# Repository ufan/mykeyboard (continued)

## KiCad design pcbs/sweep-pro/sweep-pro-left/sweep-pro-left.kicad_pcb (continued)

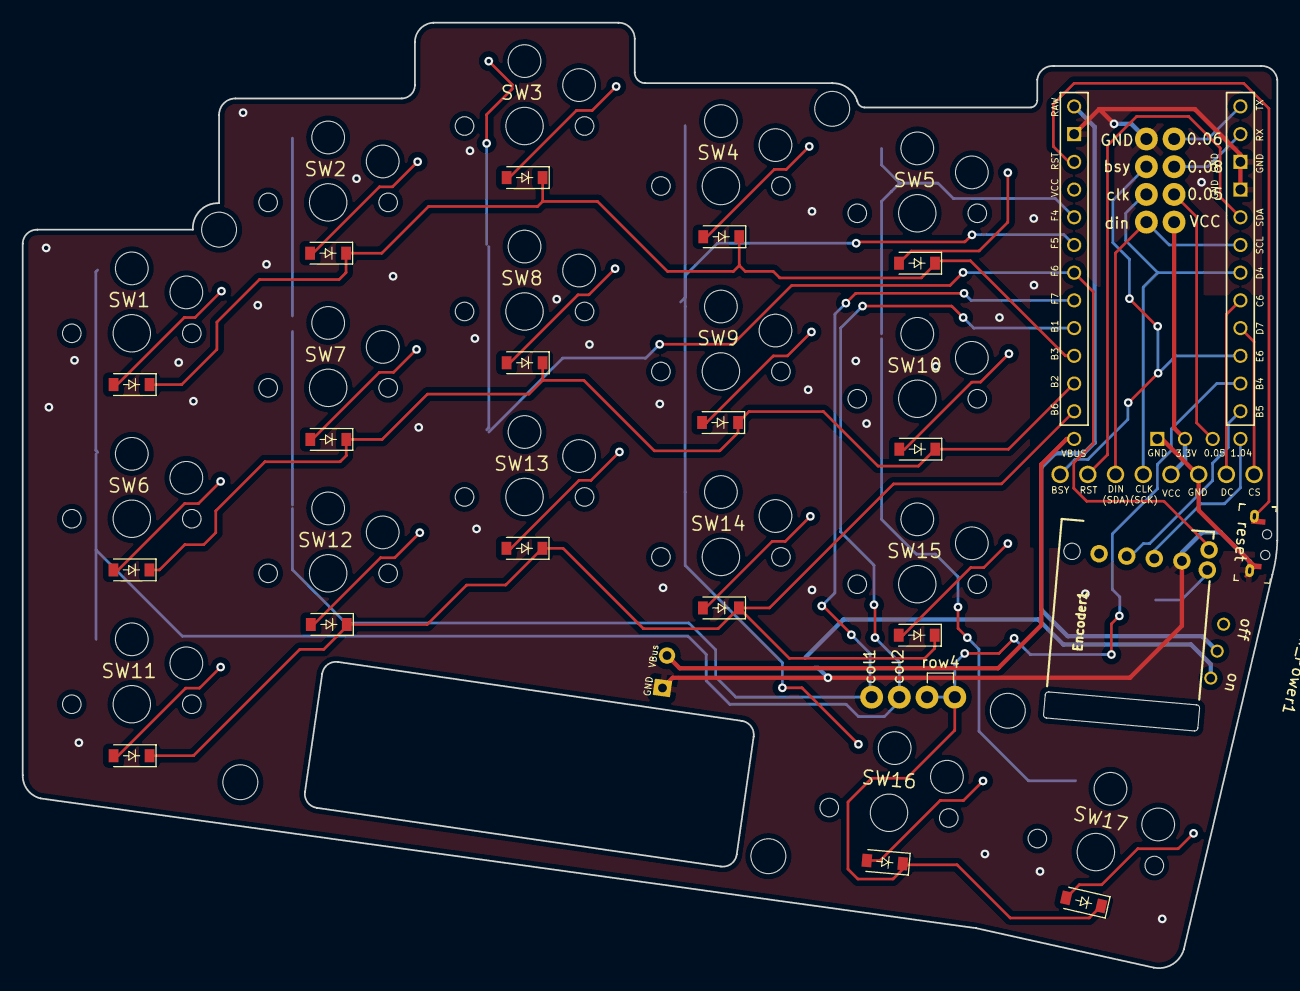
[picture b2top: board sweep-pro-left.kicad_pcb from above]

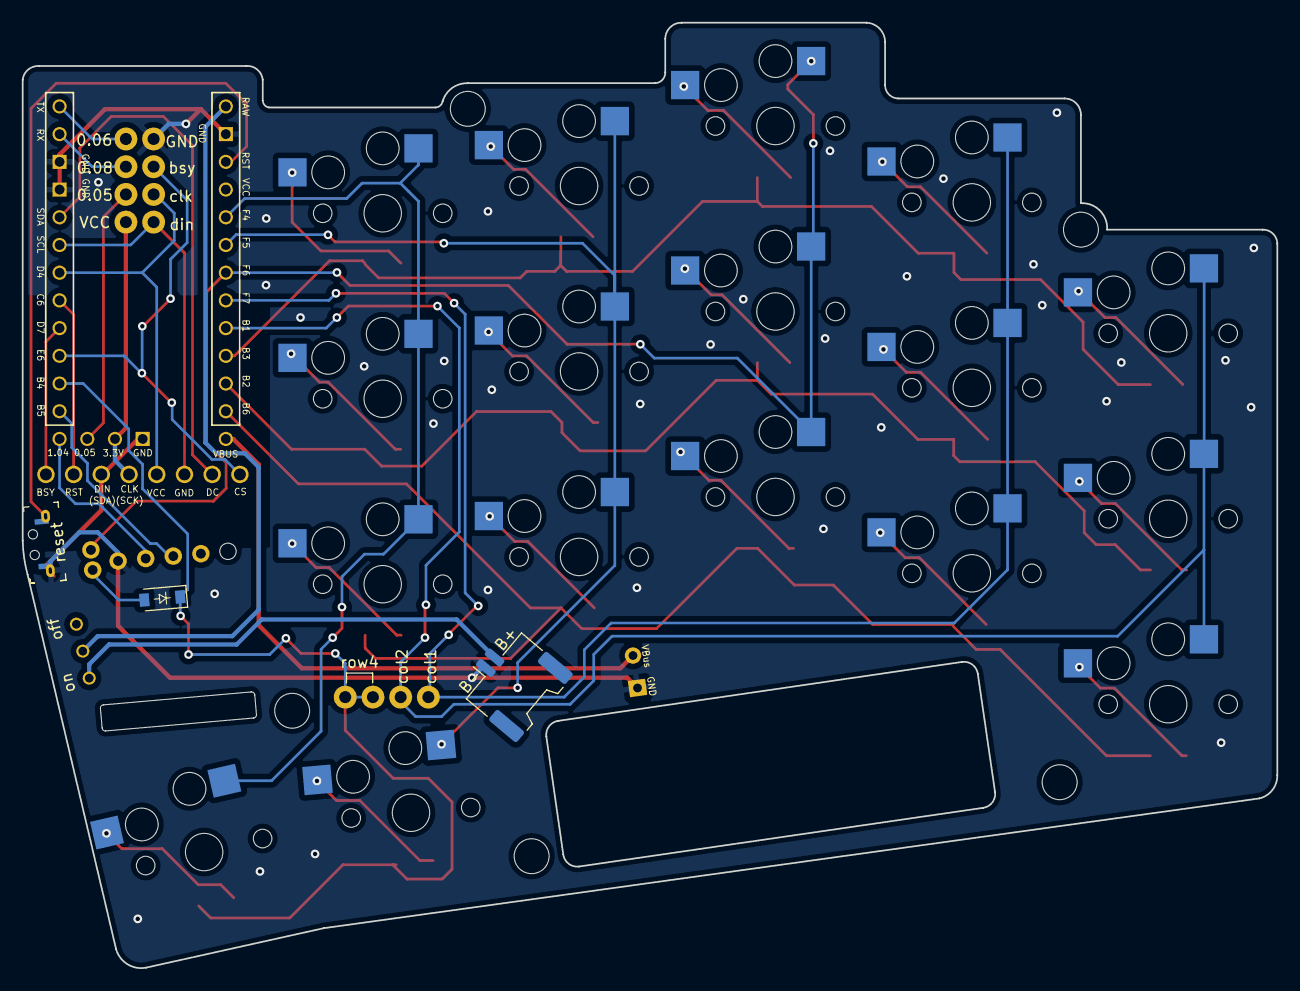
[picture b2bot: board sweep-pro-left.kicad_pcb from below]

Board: 2 copper layers, 115.0 x 86.7 mm, 50 parts (2 on the bottom side), 44 nets.

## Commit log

2022-06-05 A collection of keyboard pcbs designed by me
2022-06-06 backup
2022-06-06 init version of outline
2022-06-07 first version with complete routing
2022-06-07 outline and routing finished
2022-06-07 add 3d model
2022-06-08 add filled area (complete board)
2022-06-08 add 3d models
2022-06-08 change the position of battery connector for better case design. and change the angle of thumb cluster and board outline for better looking.
2022-06-10 bugfix
2022-06-10 add gerber zip
2022-06-11 change mouting hole diameter to 3.2mm
2022-06-11 change switch slot width from 14.1 to 14 mm
2022-06-22 archive sweep-pro as communitiy edition
2022-06-22 add sweep-pro community edition
2022-06-27 sweepro-left intial finished version
2022-06-28 sweepro v2
    1. add three expansion ports (pogopin connection)
    2. remev battery extra port
    3. use nrfmacro-lite partial footprint
    4. new power switch
    5. re-position reset button
    6. seperate board for left and right split
2022-06-29 finish left-split of corne-pro using nrfmicro as mcu
2022-06-29 add battery switch slot
2022-06-29 add a con port using jst ach connector
2022-06-29 add gerber zip file
2022-07-03 remove ground fill around anntena and tweak the anntena hole
2022-07-03 clean up
2022-07-04 finish right split of corne-pro
2022-07-06 add sweepro adaptor board
2022-07-06 update gerbers
2022-07-08 remove extra swithes from sweepro-adaptor due to jlc extra charge
2022-07-08 single swithes pcb
2022-07-15 add layout picture of palm180
2022-07-17 add corne logo mark picture
2022-07-21 [sweep-pro] correct the position of the encoder in right split
2022-08-13 backup :
2022-08-13 [sweep-pro] modify the encoder position on right side and add the correct gerber file
2022-08-13 [sweep-pro] rename the outdated right gerber
2022-09-02 [change] hotplug socket outline, does not affect pcb fabrication file
2022-09-17 [trackball-right] init version of valid schematics
2022-09-21 init version with integrated trackball in thumb position
2022-09-22 add blade keyboard (right, 38 keys, 5x3+2+2)
2022-09-23 add blade-right with trackball in thumb position
2022-09-23 add blade right with only keys
2022-09-23 add blade right with only keys (3x5)
2022-09-23 add blade with trackball on the external thumb position
2022-11-04 seperate directory for breakout pcbs
2022-12-30 add readme
2023-03-10 update readme. add new photo
2023-03-10 add picture
